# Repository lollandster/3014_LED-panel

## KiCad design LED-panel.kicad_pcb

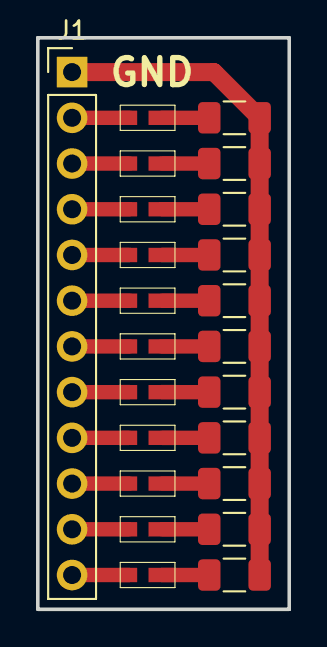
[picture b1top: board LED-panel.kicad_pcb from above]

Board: 2 copper layers, 14.0 x 31.8 mm, 23 parts (0 on the bottom side), 23 nets.

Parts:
D1, D2, D3, D4, D5, D6, D7, D8, D9, D10, D11: LED; 3014-LED
J1: Conn_01x12; PinHeader_1x12_P2.54mm_Vertical
R1, R2, R3, R4, R5, R6, R7, R8, R9, R10, R11: 4K7; R_1206_3216Metric

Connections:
GND: J1.1, R1.2, R2.2, R3.2, R4.2, R5.2, R6.2, R7.2, R8.2, R9.2, R10.2, R11.2
unnamed: D1.1, R1.1
unnamed: D1.2, J1.2
unnamed: D2.1, R2.1
unnamed: D2.2, J1.3
unnamed: D3.1, R3.1
unnamed: D3.2, J1.4
unnamed: D4.1, R4.1
unnamed: D4.2, J1.5
unnamed: D5.1, R5.1
unnamed: D5.2, J1.6
unnamed: D6.1, R6.1
unnamed: D6.2, J1.7
unnamed: D7.1, R7.1
unnamed: D7.2, J1.8
unnamed: D8.1, R8.1
unnamed: D8.2, J1.9
unnamed: D9.1, R9.1
unnamed: D9.2, J1.10
unnamed: D10.1, R10.1
unnamed: D10.2, J1.11
unnamed: D11.1, R11.1
unnamed: D11.2, J1.12

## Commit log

2018-10-07 moved text to bottom silkscreen
2018-10-07 small mod on text
2018-10-07 text font changed to Times New Roman on the bottom side silkscreen. Done using svg2mod
